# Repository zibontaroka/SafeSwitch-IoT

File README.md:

# ⚡ SafeSwitch-IoT: A Secure IoT-Based Control Handover System for Power Line Maintenance

This repository contains the full implementation of an **IoT-based Smart Power Control Handover System** that enhances **lineman safety** in power distribution networks.  
The system introduces a **formalized handover protocol** where Operators can delegate control of electrical zones/feeders to Linemen, ensuring safe maintenance by preventing accidental re-energization.

---

## 📑 Table of Contents
- [Overview](#-overview)
- [Key Features](#-key-features)
- [Technology Stack](#️-technology-stack)
- [Hardware and PCB Design](#-hardware-and-pcb-design)
- [File Structure](#-file-structure)
- [Getting Started](#-getting-started)
- [Usage](#-usage)
- [Contributing](#-contributing)
- [License](#-license)
- [Contact](#-contact)

---

## 📖 Overview
Power line maintenance is inherently dangerous, particularly in developing regions such as **Bangladesh**, where standardized safeguards are limited.  
One major risk arises when Operators unintentionally re-energize lines under maintenance, causing **severe injury or fatality** for Linemen.  

✅ Our proposed solution:  
A **secure IoT-based control handover system** that ensures Operators **cannot switch relays** in a zone once it is handed over to a Lineman.  
Control is restored only after the Lineman safely revokes access via a **PIN-authenticated interface**.

---

## ✨ Key Features
- 🔐 **Secure Control Handover** – Operator-to-Lineman delegation with mutual exclusion.  
- 👤 **Role-Based Access Control (RBAC)** – Enforces permissions per role.  
- ⚡ **Real-Time Communication** – WebSocket-based low-latency updates.  
- 🔑 **PIN-Based Authentication** – Prevents unauthorized relay operations.  
- 📝 **Auditability & Traceability** – Logs every critical action with user ID, timestamp, feeder/zone.  
- 📈 **Modular & Scalable** – Easily extendable for more devices/zones.  

---

## ⚙️ Technology Stack
**Backend:** Node.js · Express.js · PostgreSQL · WebSocket  
**Frontend:** HTML · CSS · JavaScript  
**Hardware:** ESP8266 · LM2596 Buck Converter · 2N2222 NPN Transistor · 1N4007 Diode · Relays  

---

## 🖥️ Web Application Interface

### Operator Dashboard
Centralized control center for system operators to monitor and manage power distribution network.

**Key Functionalities:**
- 📊 **Real-time Monitoring** - Live status of all feeders and zones
- 🔄 **Control Handover** - Safe delegation to linemen for maintenance
- 🚨 **Emergency Override** - Critical situation management
- 📈 **System Analytics** - Performance metrics and usage statistics
- 👥 **User Management** - Lineman assignment and role management

**Interface Components:**
1. **Sidebar Navigation** - Quick access to different sections
2. **Dashboard Overview** - System-wide status at a glance  
3. **Feeder Control Panel** - Individual zone management
4. **Handover History** - Audit trail of all control transfers
5. **Alert System** - Real-time notifications and warnings

### Lineman Dashboard
Secure, PIN-protected interface for field technicians during maintenance operations.

**Key Functionalities:**
- 🔐 **PIN Authentication** - Secure access to assigned zones
- ⚡ **Relay Control** - Direct control over circuit breakers
- 📱 **Mobile-Friendly** - Optimized for field use
- 🔄 **Status Sync** - Real-time synchronization with backend
- ✅ **Safety Lock** - Prevents accidental operations

**Security Features:**
- Session timeout after inactivity
- PIN-based re-authentication required
- Control limited to assigned zones only
- Audit log of all operations
- Emergency stop functionality

### Workflow Demonstration
**Control Handover Process:**
1. Operator initiates handover from their dashboard
2. Lineman receives notification and enters PIN
3. Control transfers to lineman (operator access locked)
4. Lineman performs maintenance operations
5. Lineman revokes control after completion
6. Operator regains full control automatically

---

## 🔧 Hardware and PCB Design

The **ESP8266 control module** manages up to **7 relays** for breaker/switch control.  
It authenticates with the backend and executes Operator/Lineman commands securely.  

### Relay Control Module
- Authentication with backend  
- Relay switching via GPIO  
- Real-time state reporting  

**Schematic Diagram:**  

**PCB Layout:**  

🔗 KiCad project & Gerber files are in the [`PCB_design/`](./PCB_design/) directory.  

---

## 📂 File Structure
```

smart-power-handover-system/
├── database/        # PostgreSQL backup (powergrid\_backup.sql)
├── firmware/        # ESP8266 Arduino firmware
├── PCB\_design/      # Hardware design (KiCad + Gerber)
├── photos/          # PCB & schematic images
├── web\_app/         # Web application (frontend + backend)
├── admin/       # Admin dashboard & user management
├── operator/    # Operator control dashboard
├── lineman/     # Lineman PIN-secured dashboard
├── viewer/      # Viewer-only monitoring UI
├── backend/     # Node.js backend (Express + WebSocket)
├── css/         # Stylesheets
├── js/          # Frontend JS logic
└── images/      # UI assets/icons

```

---

## 🚀 Getting Started

### Prerequisites
- [Node.js](https://nodejs.org/) (>= 18.x)  
- [PostgreSQL](https://www.postgresql.org/)  

### Installation

1. **Clone the repository:**
   ```bash
   git clone https://github.com/zibontaroka/SafeSwitch-IoT.git
   cd smart-power-handover-system/web_app/backend
   ```

2. **Install dependencies:**
   ```bash
   npm install
   ```

3. **Set up the database:**
   - Create a PostgreSQL database
   - Import the backup:
     ```bash
     psql -U your_user -d your_db -f ../../database/powergrid_backup.sql
     ```

4. **Configure environment variables:**
   Create `.env` file in `web_app/backend/` directory with:
   ```env
   DB_USER=your_db_user
   DB_HOST=your_db_host
   DB_DATABASE=your_db_name
   DB_PASSWORD=your_db_password
   DB_PORT=your_db_port
   JWT_SECRET=your_jwt_secret
   ```

5. **Start the server:**
   ```bash
   npm start
   ```

---

## 📖 Usage (Control Workflow)

1. **Initiation** → Operator selects feeder/zone & assigns to a Lineman.
2. **Delegation** → Zone marked as `control_active = TRUE`, blocking Operator actions.
3. **Execution** → Lineman controls relays via PIN-authenticated dashboard.
4. **Revocation** → Lineman revokes control (PIN entry → `control_active = FALSE`).
5. **Restoration** → Operator regains full control.

---

## 🤝 Contributing

Contributions, feature requests, and bug reports are welcome!
Please open an **issue** or submit a **pull request**.

---

## 📄 License

This project currently has **no license**.
(You may add `MIT`, `Apache-2.0`, or another license in a [LICENSE](LICENSE) file.)

---

## 📞 Contact

📧 Md Shaifulla Zibon
🔗 [LinkedIn](https://www.linkedin.com/in/md-shaifulla-zibon/)

---

"# SafeSwitch-IoT"

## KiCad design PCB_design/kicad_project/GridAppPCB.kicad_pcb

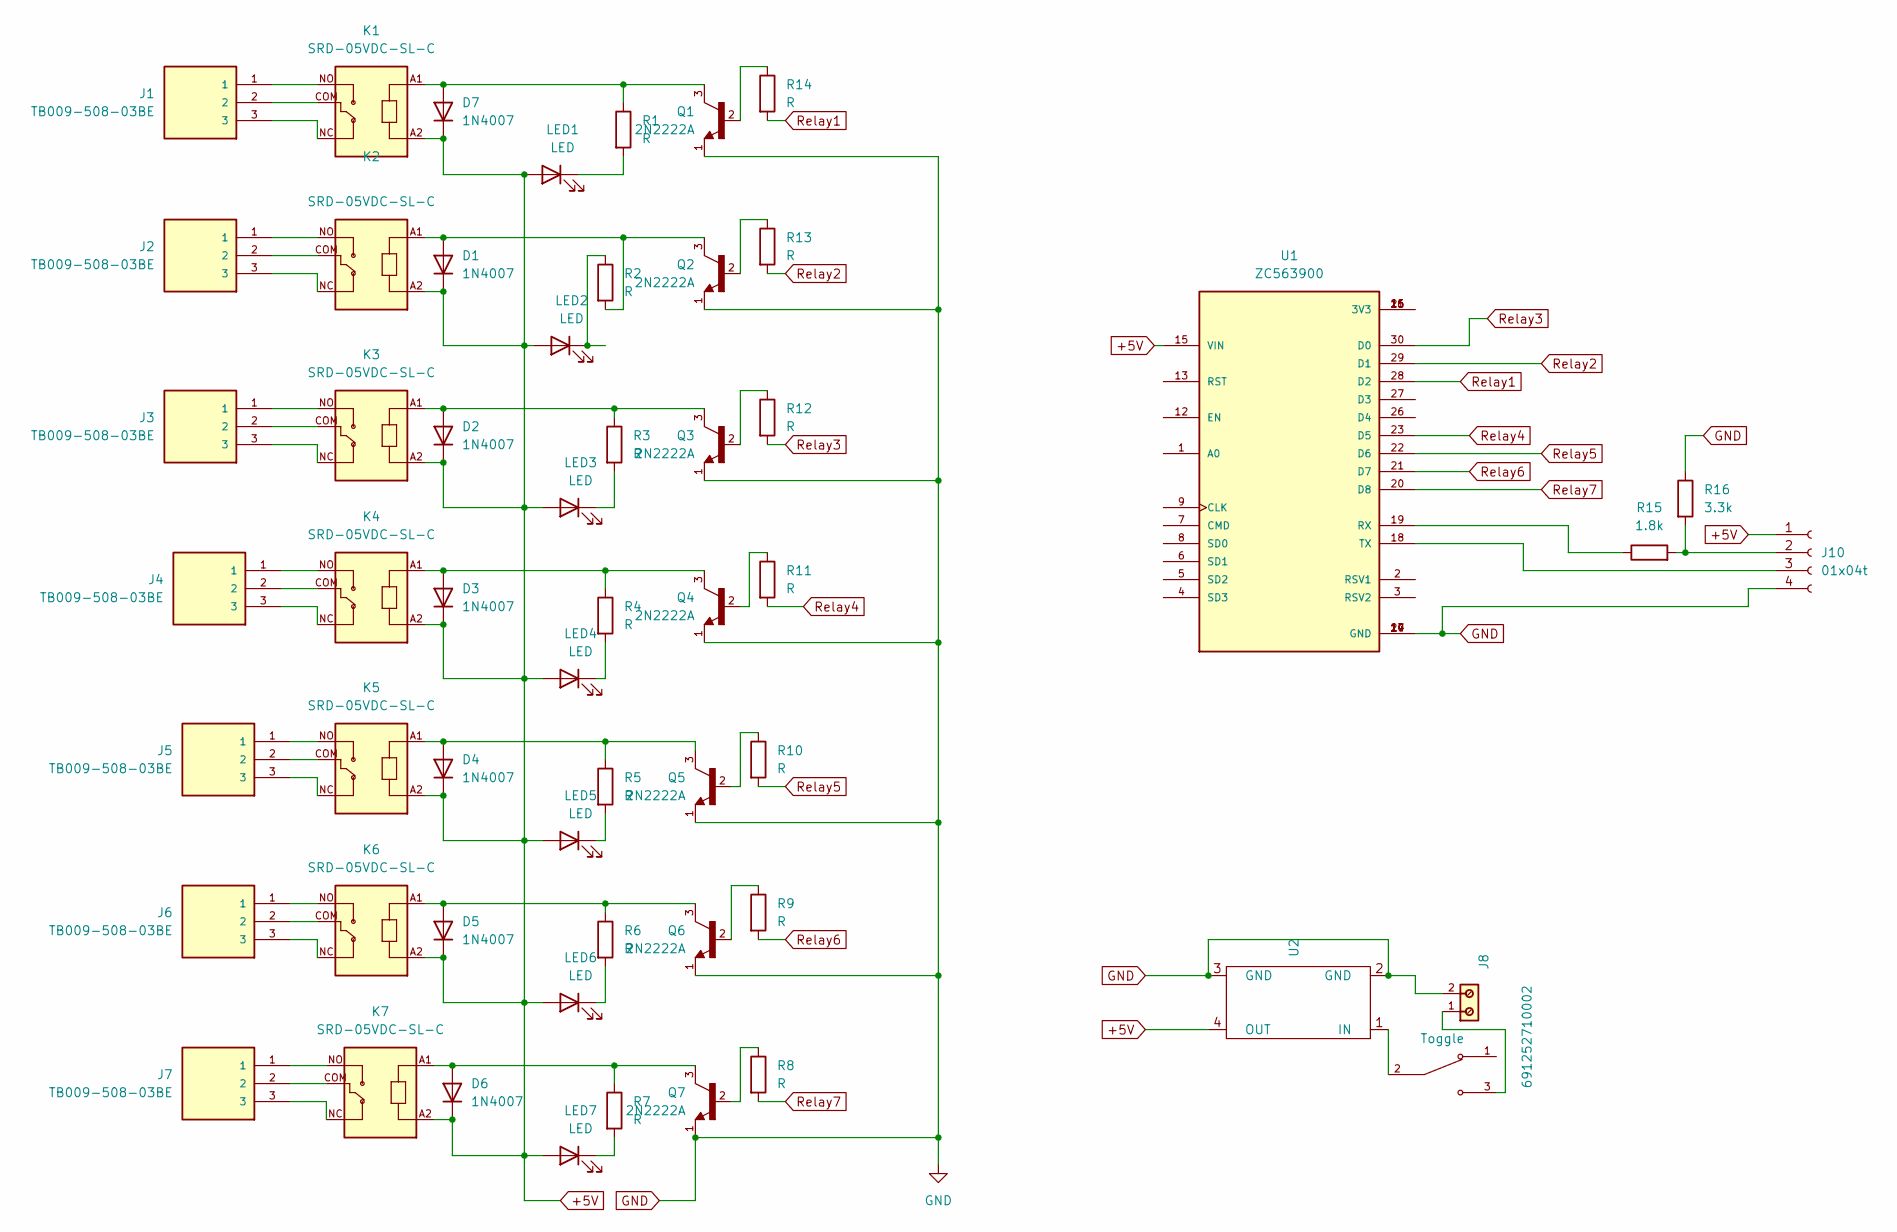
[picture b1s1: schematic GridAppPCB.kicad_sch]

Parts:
D1, D2, D3, D4, D5, D6, D7: 1N4007; D_DO-41_SOD81_P10.16mm_Horizontal
J1, J2, J3, J4, J5, J6, J7: TB009-508-03BE; TerminalBlock_CUI_TB007-508-03_1x03_P5.08mm_Horizontal
J8: 691252710002; Altech_AK100_1x02_P5.00mm; PART-NUMBER 691252710002
J10: 01x04t; PinSocket_1x04_P2.54mm_Vertical
K1, K2, K3, K4, K5, K6, K7: SRD-05VDC-SL-C; RELAY_SRD-05VDC-SL-C
LED1, LED2, LED3, LED4, LED5, LED6, LED7: LED; LED_D5.0mm
Q1, Q2, Q3, Q4, Q5, Q6, Q7: 2N2222A; TO92254P470H750-3; PARTREV N/A
R1, R2, R3, R4, R5, R6, R7, R8, R9, R10, R11, R12, R13, R14: R; R_Axial_DIN0207_L6.3mm_D2.5mm_P7.62mm_Horizontal
R15: 1.8k; R_Axial_DIN0207_L6.3mm_D2.5mm_P7.62mm_Horizontal
R16: 3.3k; R_Axial_DIN0207_L6.3mm_D2.5mm_P7.62mm_Horizontal
S9: Toggle; SW_100SP1T1B1M1QEH; PARTREV D
U1: ZC563900; MODULE_ZC563900; PARTREV 1.0
U2: YAAJ_DCDC_StepDown_LM2596

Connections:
+5V: D1.1 (K), D2.1 (K), D3.1 (K), D4.1 (K), D5.1 (K), D6.1 (K), D7.1 (K), J10.1, K1.A2, K2.A2, K3.A2, K4.A2, K5.A2, K6.A2, K7.A2, LED1.2 (A), LED2.2 (A), LED3.2 (A), LED4.2 (A), LED5.2 (A), LED6.2 (A), LED7.2 (A), U1.15 (VIN), U2.4 (OUT)
GND: J8.2, J10.4, Q1.1, Q2.1, Q3.1, Q4.1, Q5.1, Q6.1, Q7.1, R16.1, U1.10 (GND), U1.14 (GND), U1.17 (GND), U1.24 (GND), U2.2 (GND), U2.3 (GND)
unnamed: D1.2 (A), K2.A1, Q2.3, R2.2
unnamed: D2.2 (A), K3.A1, Q3.3, R3.1
unnamed: D3.2 (A), K4.A1, Q4.3, R4.1
unnamed: D4.2 (A), K5.A1, Q5.3, R5.1
unnamed: D5.2 (A), K6.A1, Q6.3, R6.1
unnamed: D6.2 (A), K7.A1, Q7.3, R7.1
unnamed: D7.2 (A), K1.A1, Q1.3, R1.1
unnamed: J1.1, K1.NO
unnamed: J1.2, K1.COM
unnamed: J1.3, K1.NC
unnamed: J2.1, K2.NO
unnamed: J2.2, K2.COM
unnamed: J2.3, K2.NC
unnamed: J3.1, K3.NO
unnamed: J3.2, K3.COM
unnamed: J3.3, K3.NC
unnamed: J4.1, K4.NO
unnamed: J4.2, K4.COM
unnamed: J4.3, K4.NC
unnamed: J5.1, K5.NO
unnamed: J5.2, K5.COM
unnamed: J5.3, K5.NC
unnamed: J6.1, K6.NO
unnamed: J6.2, K6.COM
unnamed: J6.3, K6.NC
unnamed: J7.1, K7.NO
unnamed: J7.2, K7.COM
unnamed: J7.3, K7.NC
unnamed: J8.1, S9.3
unnamed: J10.2, R15.2, R16.2
unnamed: J10.3, U1.18 (TX)
unnamed: LED1.1 (K), R1.2
unnamed: LED2.1 (K), R2.1
unnamed: LED3.1 (K), R3.2
unnamed: LED4.1 (K), R4.2
unnamed: LED5.1 (K), R5.2
unnamed: LED6.1 (K), R6.2
unnamed: LED7.1 (K), R7.2
unnamed: Q1.2, R14.1
unnamed: Q2.2, R13.1
unnamed: Q3.2, R12.1
unnamed: Q4.2, R11.1
unnamed: Q5.2, R10.1
unnamed: Q6.2, R9.1
unnamed: Q7.2, R8.1
unnamed: U1.11 (3V3), U1.16 (3V3), U1.25 (3V3)
unnamed: R15.1, U1.19 (RX)
unnamed: S9.2, U2.1 (IN)
Relay1: R14.2, U1.28 (D2)
Relay2: R13.2, U1.29 (D1)
Relay3: R12.2, U1.30 (D0)
Relay4: R11.2, U1.23 (D5)
Relay5: R10.2, U1.22 (D6)
Relay6: R9.2, U1.21 (D7)
Relay7: R8.2, U1.20 (D8)

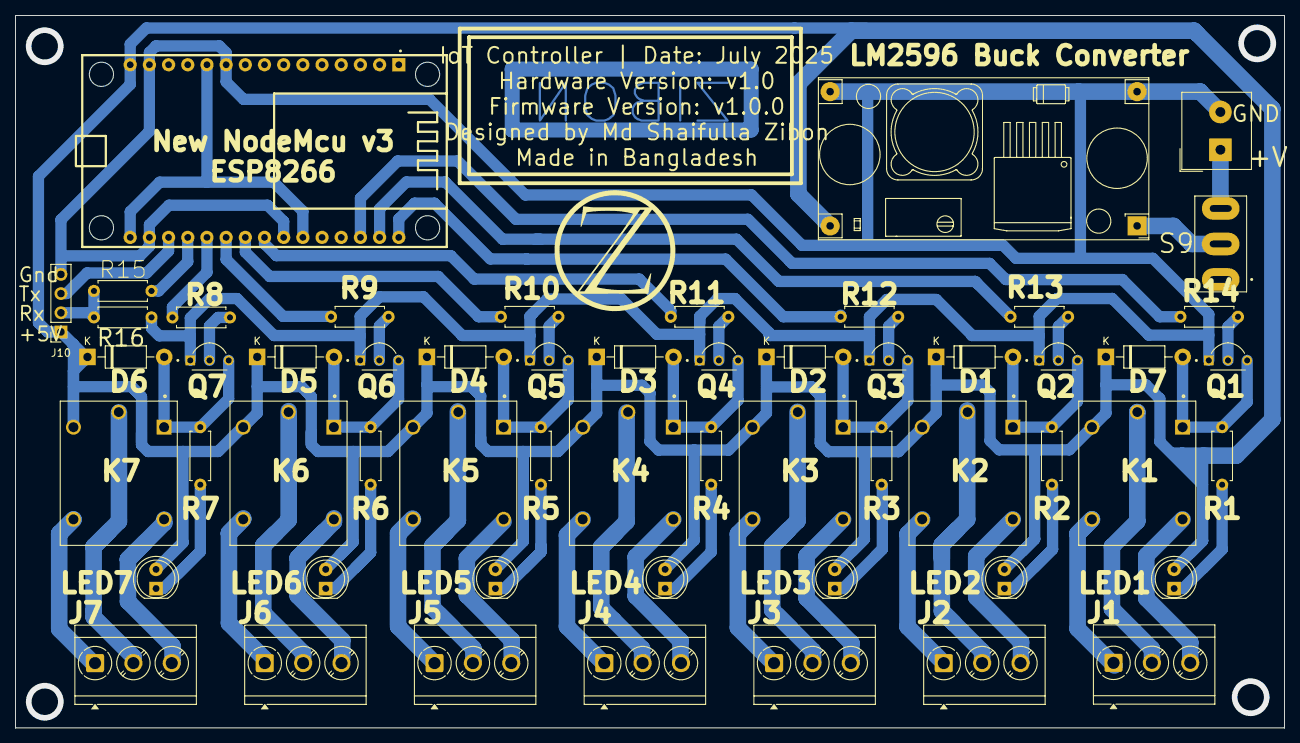
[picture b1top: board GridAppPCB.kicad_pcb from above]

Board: 2 copper layers, 168.0 x 94.3 mm, 56 parts (0 on the bottom side), 57 nets.

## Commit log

2025-10-01 Add complete project: IoT Power Control Handover System with PCB design, firmware, and web application
2025-10-01 README.md
2025-10-01 Rename Oparator dashboard.JPG to Oparator-dashboard.JPG

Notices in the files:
README.md:
License: Pending
